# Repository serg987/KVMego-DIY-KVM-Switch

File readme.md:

# KVM Switch and related projects

## Quick links:

[KVM Switch - ATMega Microship studio project](kvm_switch/)

[KVM Switch - Kicad project](kvm_switch/pcb_kicad/)

[Video switches in general](video_switches/)

[I2C Switch - A hack for EDID sharing, ATTiny85 project](video_switches/i2c_switch/)

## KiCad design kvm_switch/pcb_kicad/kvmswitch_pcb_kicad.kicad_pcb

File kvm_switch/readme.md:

# KVMego KVM Switch

## Why?

The market for KVM switches is quite wide, but it is difficult to find one that properly fits someone's needs. The main disadvantage is that they are manufactured as single units, where video and keyboard/mouse switches are housed in the same enclosure. This not only forces users to deal with numerous thick cables but also limits their options. Some switches may have EDID support but lack hotkey support, while others may not have enough display ports or support for needed resolutions. However, the main problem is that most switches implement just an ordinary USB switch that disconnects displays, keyboards, and mice from inactive computers, making it possible to detect when the switch is being used. Additionally, KVM switches usually do not support a mouse jiggler function, which allows inactive computers to stay awake while not in use.

This project attempts to resolve most of these issues.

## Description

### Main Features:
- **Modular architecture**: The keyboard/mouse control unit is separated from video switches, allowing users to either use existing switches or create custom video switches. A video switch may be directly plugged into a monitor, requiring fewer thick video cables.
- **Persistent USB connection**: Once the KVM switch is connected to a computer's USB port, it is never disconnected, making it impossible to detect switching by disconnection.
- **Integrated controls**: All controls and indicators are built into the keyboard; no separate buttons or LEDs are needed. The unit can be hidden from view.
- **Built-in mouse jiggler**: Keeps computers awake, both active and inactive ones.
- **Cost-effective components**: Uses development modules that require no high-precision soldering.
- **Plain C ATMega code**: No USB stack required, easily adaptable to individual needs.

### Known Limitations:
- **USB wire connections**: The unit connects to computers via USB wires. Not many keyboard and mouse types have been tested, but it has worked with all tested devices, including wireless mice with 2.4GHz USB dongle.
- **USB-only switching**: Only USB keyboards and mice can be switched between computers. However, with an external USB switch and some adaptation, other devices may be connected.
- **No VID/PID copying**: A computer will see a standard HID device with the CH9350L signature rather than the original device signature.
- **Processing delays**: USB-UART-CPU-UART-USB processing introduces delays up to several dozen milliseconds, though this is not noticeable during normal use.
- **Video switch requirement**: Still requires video switches. Existing switches must be adapted to use plain on/off signals or require code adaptation. RF-controlled custom video switches are supported via RF transmitter code.
- **Three-computer limit**: Currently supports up to 3 computers.
- **HID packet structure dependency**: Different HID devices have varying UART packet structures, which is critical for the jiggler function. Currently, 4 types of mouse packets are recognized, so the jiggler may not work with some mice, though main switch functionality should remain unaffected.
- **No hot-plugging**: Due to different mouse types, mice cannot be hot-plugged as the jiggler may stop working. The switch must be fully disconnected from all computers to change the mouse.

## Compiling and programming

The project uses Microchip Studio as the IDE, so all settings are configured there. By default, it targets the ATMega2560 with the 'DEBUG' configuration, which produces slightly larger code. If debugging is not needed, switch to the 'Release' target for optimized builds.

Fuses for ATMega:

### Build Configuration Options:

#### LCD_DEBUG
When `LCD_DEBUG` is defined in `src/common/config.h`, the system enables debug information output to a 1602 LCD display. This feature:
- Displays error messages and system status information
- Shows various error codes including:
  - `E: UnknCmdM XX` - Unknown command byte from master (XX = hex value)
  - `E: UnknCmdS X XX` - Unknown command byte from slave (X = channel, XX = hex value)
  - `E: KbMsDaSzEx XX` - Keyboard/Mouse data size exceeded (XX = size)
  - `E: VPSizeEx XX` - VID/PID data size exceeded (XX = size)
  - `E: QueueOvrflw` - Scheduler queue overflow
- When LCD is not going to be used, comment out `#define LCD_DEBUG` in config.h

#### RF_TRANSMITTER
When `RF_TRANSMITTER` is defined in `src/common/config.h`, the video control lines become active (low level) for 2 seconds only during
the switching. This allow to contol the 433MHz RF encoded transmitter with 4 buttons:
- See `videoSwitchControl.c` for implementation details
- For simple continuous high-level video control signals, comment out `#define RF_TRANSMITTER` in config.h

## User Manual

### Initial Setup
Always connect the device to a PC with the operating system turned on, logged in, and not in sleep mode. There have been reported issues with macOS (likely hardware-related and possibly connected to power management) where the CH9350L fails to initialize. See the Known Issues section for details.

### LCD Display Messages
If an LCD is connected and `LCD_DEBUG` is enabled, you will see various status and error messages:

**System Status Messages:**
- Normal operation displays current PC connection status
- Error messages appear when issues occur (see LCD_DEBUG section above)
- Messages alternate between lines to show multiple pieces of information

**Error Indicators:**
- Errors are displayed with prefixes like "E: " followed by specific error codes
- Unknown command errors show the problematic byte value in hexadecimal
- Size exceeded errors indicate buffer overflows
- Queue overflow indicates the scheduler is overloaded

### Single PC Usage
The device can be used with a single PC if only the jiggler functionality is needed without additional device connections.

### Control Interface
Everything is controlled by double-pressing the 'ScrollLock' button, which starts the control sequence.

#### Control Sequence:
1. **Initiate control mode**: Double-press 'ScrollLock'
2. **Visual feedback**: All three keyboard LEDs will blink once
3. **Current state display**: LEDs will blink to show the current switching mode state (e.g., if current PC is 2, the CapsLock LED will blink)
4. **Command input**: You can proceed with a command without waiting for the blinking to stop
5. **New state confirmation**: After state change, LEDs will blink to show the new state
6. **Error indication**: If there's an error (requested PC not connected or unsupported control button), all 3 LEDs will blink rapidly
7. **Auto-exit**: The device automatically exits control mode after 6 seconds of inactivity
8. **LED restoration**: After exiting control mode, LEDs return to displaying the keyboard state of the connected PC

#### PC Switching Commands:
- `2 × ScrollLock + [1-3]` - Switch to PC connected to the corresponding port
- `2 × ScrollLock + 0` (or `+` or `Enter`) - Rolling switch to the next PC with increasing number
- `2 × ScrollLock + -` - Rolling switch to the next PC with decreasing number

*Note: Numeric keys, +/- keys, and Enter work from both the main keyboard layout and the numpad.*

#### Jiggler Control:
The jiggler simulates mouse movements as arcs with random speed, length, and time between movements to prevent computers from entering sleep mode.

**Jiggler Control Mode:**
- Access: `2 × ScrollLock + J`
- **Confirmation**: All LEDs blink once after pressing 'J'
- **Toggle functionality**: Unlike PC switching, jiggler can be toggled on and off for each PC
- **State display**: Shows current jiggler state by blinking LEDs for PCs where jiggler is active
- **No active indication**: If no PC has active jiggler, no LEDs will blink before or after commands

**Jiggler Commands:**
- `2 × ScrollLock + J + [1-3]` - Toggle jiggler for the corresponding PC
- `2 × ScrollLock + J + 0` - Toggle jiggler for the current PC

**Jiggler Timing:**
- **Active PC**: When jiggler is enabled for the currently connected PC, it waits 2 minutes after the last mouse movement or keypress before starting
- **Inactive PC**: When jiggler is enabled for an inactive PC, it starts with the next scheduled jiggler cycle (maximum 25 seconds)

## Video Switches

Video switches should be connected to the video control output. In most cases, this requires a custom solution. The author used inexpensive HDMI switches with added RF receivers to reduce cable clutter. This option will be described in the repository documentation (to be added later), but any solution suitable for a user's setup can be implemented.

The system provides three on/off outputs for controlling video switches, connected via a USB-C connector for the video control cable. **Note**: This is NOT a USB connection; USB-C cables are used purely for convenience due to their thin profile when connecting to video and/or USB switches.

## Schematics

### Design
To avoid working with embedded USB stacks, CH9350L ICs are used for USB communication. These ICs function as host/master HID-class USB devices and convert USB packets to UART packets. The system uses 4 CH9350L chips: one master device for keyboard and mouse connection, and 3 for computer connections. If only 2 computers are needed, only 3 CH9350L chips are required.

### Core Components
**CPU**: ATMega640/1280/2560 processes all UART packets, controls data flow, and prepares jiggler sequences.

**Why ATMega?** 
- Has exactly the computing power needed for this application
- Lacks peripherals that could potentially leak user data (critical for keyboard security)
- One of a few available microcontrollers on the market with 4 hardware UARTs at a reasonable price and a lot of development boards
- Available development boards make prototyping easier
- Author's familiarity with the platform

### Power Management
The +5V power from computers is isolated using Schottky diodes and processed through a DC-DC step-up converter to maintain +5.0V. This is optional - the prototype board worked without the converter using only Schottky diodes, operating at Vcc~4.7V.

### Debug and Development Features
The schematic and board include:
- **10-pin connector**: For 8-channel logic analyzer
- **ISP** and **JTAG** connectors: For programming and debugging
- **1602 LCD**: Displays debug information (not required for normal operation)
- **Connection monitoring resistors** (R18-R20 and R22-R24): For monitoring computer connections (not currently used in code, reserved for future edge case handling)

### Implementation Options

#### Development Board Implementation
The unit can be implemented using prototype boards with development modules. Various modules for ATMega2560 and CH9350L are available on Aliexpress and other marketplaces.

**Important considerations:**
- Most ATMega2560 modules use 16 MHz crystal resonators, which must be replaced with 14.7456 MHz ones
- Development boards typically have USB-UART chips connected to UART0 pins - either remove their resistors or cut the PCB tracks

The first hardware prototype used development boards

The original Aliexpress links used by author are no longer available, probably due to US tariffs, but something similar has been found:
 - Mega 2560 PRO MINI Board - https://www.aliexpress.us/item/3256807606413251.html
 - CH9350L module with 2xUSB-A sockets https://www.aliexpress.us/item/3256806492553287.html
 - USB-A M to USB-B F adapter https://www.aliexpress.us/item/3256805907770571.html

#### Custom PCB Implementation
The custom PCB includes both USB-B and USB-C footprints for computer connections - solder whichever connector type is suitable for your setup.

The PCB is available to order on [PCBWay](https://www.pcbway.com/project/shareproject/KVMego_A_modular_undetectable_KVM_switch_with_a_built_in_mouse_jiggler_c0eef20d.html)

### Resource Utilization

#### ATMega2560 Resources Used:
- **UART0**: 'Master' CH9350, connected to keyboard and mouse
- **UART1-3**: 'Slave' CH9350s, connected to PCs
- **TIMER4**: Exclusively for scheduler (T = ~500 μs)
- **TIMER3**: F=Fosc, for seeding random generator (may be reused after initialization, but currently not needed)

#### Component Requirements
**Essential components:**
- ATMega with crystal and supporting discrete components
- CH9350L chips with their discrete components and USB connectors
- Schottky diodes

**For prototype implementation:** Only ATMega development board and 2-4 CH9350L boards are needed. This approach avoids tedious soldering and is often cheaper than buying components separately.

## Known Issues

### Hardware Issues
**PCB Gerbers**: The PCB gerbers currently on PCBWay have a cosmetic issue - the ISP connector is incorrectly labeled as JTAG. The schematic and PCB in the repository include the JTAG connector, but this version has not gone to production.

### Software Limitations
**Mouse Hot-plugging**: Due to different mouse types sending different frame structures, mice cannot be hot-plugged as the jiggler may stop working. Reinitializing the jiggler on-the-fly is challenging and not currently implemented.

### Platform-Specific Issues
**macOS Compatibility**: 
- **Symptoms**: Exact reproduction steps are unknown, but the issue occurred when the switch was connected to a Mac via a dock station and disconnected while the Mac was in sleep mode
- **Behavior**: Upon reconnection, CH9350L fails to initialize and continuously responds with '57 AB 12 00 00 00 00 00 FF AC 20' to '57 AB 82 A3' requests
- **Resolution**: Disconnect and reconnect the dock station while the OS is awake (reconnecting the switch alone while OS is awake does not resolve the issue)

## Development

### Testing Framework
Critical code has unit test coverage located in the [atmswitch_uts](atmswitch_uts/) directory. This is a Ceedling project with setup [instructions](atmswitch_uts/test/readme.md).

### Contributing
When modifying the code:
1. Note that the main loop should be no longer than 2 bytes at 115.2Kbaud - ~170us. Even there are buffers on the receiver sides, 
the overflow would make things worse, so to be on the safe side do not allow the main loop grow. Split heavy computing tasks
on multiple steps and schedule them
2. Ensure unit tests pass for any changed modules
3. Test with multiple keyboard and mouse types if modifying input handling
4. Verify jiggler functionality
5. Test all hotkey combinations

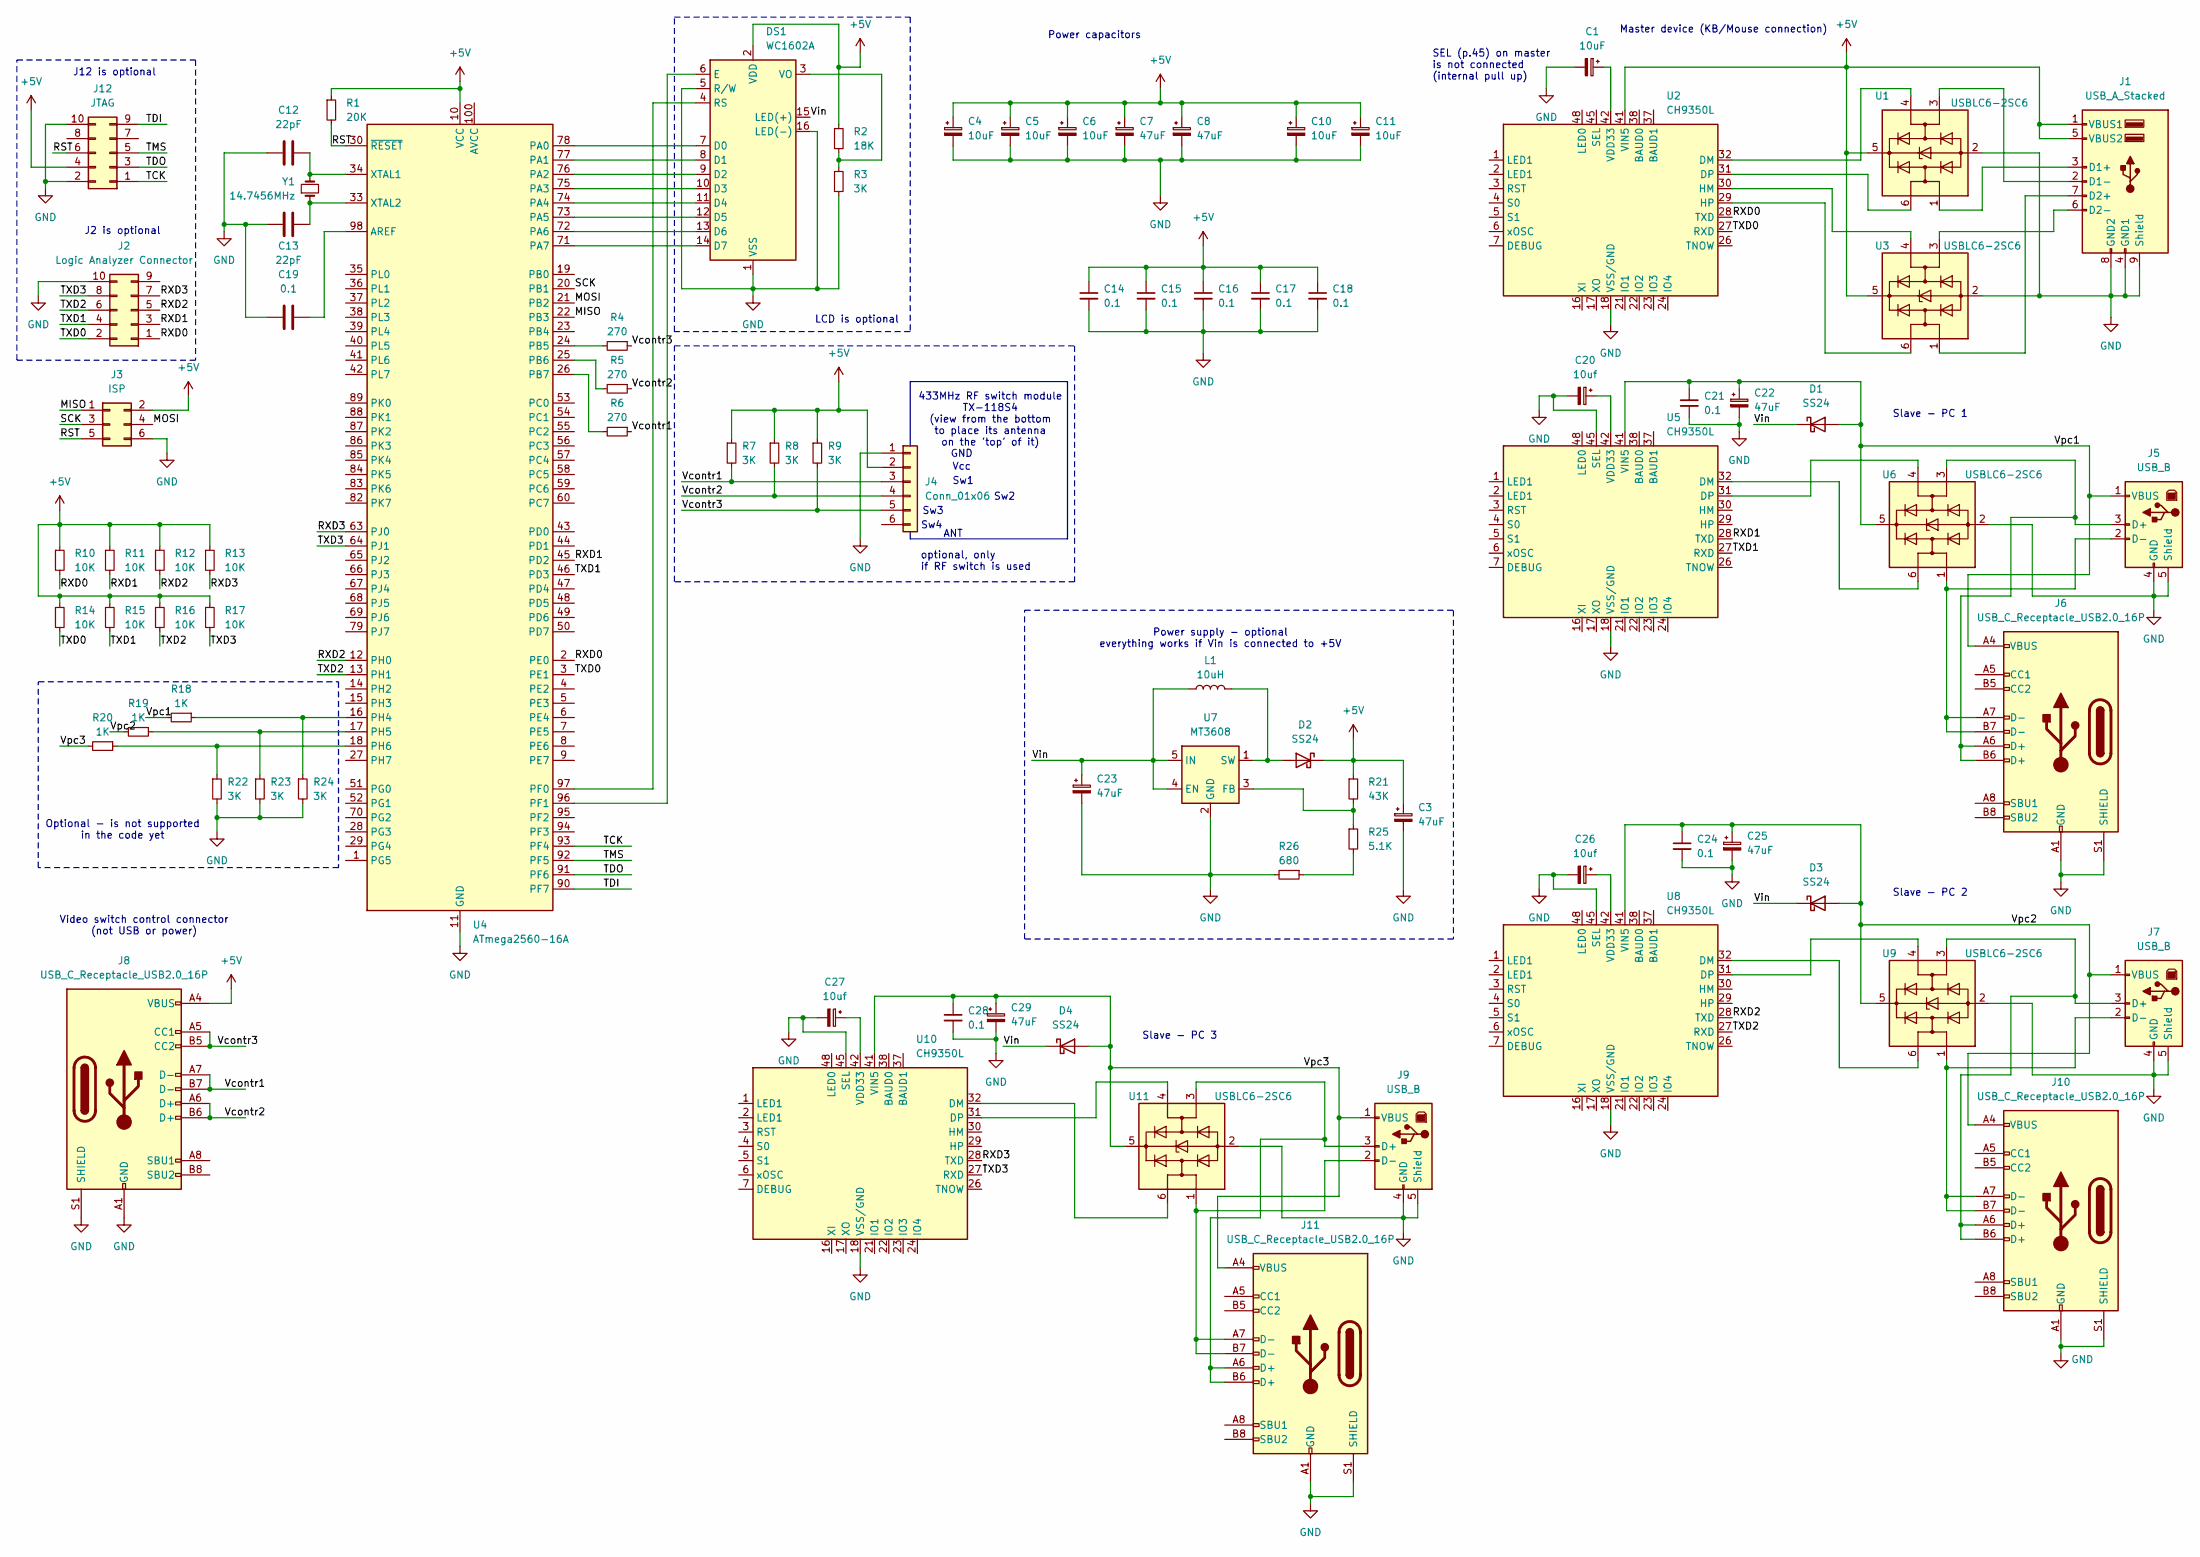
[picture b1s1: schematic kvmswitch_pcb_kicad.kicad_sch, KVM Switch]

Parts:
C1, C4, C5, C6, C10, C11: 10uF; CP_EIA-3216-12_Kemet-S_Pad1.58x1.35mm_HandSolder
C3, C7, C8, C22, C23, C25, C29: 47uF; CP_EIA-3216-12_Kemet-S_Pad1.58x1.35mm_HandSolder
C12, C13: 22pF; C_1206_3216Metric_Pad1.33x1.80mm_HandSolder
C14, C15, C16, C17, C18, C19, C21, C24, C28: 0.1; C_1206_3216Metric_Pad1.33x1.80mm_HandSolder
C20, C26, C27: 10uf; CP_EIA-3216-12_Kemet-S_Pad1.58x1.35mm_HandSolder
D1, D2, D3, D4: SS24; D_SMA_Handsoldering
DS1: WC1602A
J1: USB_A_Stacked; USB_A_Wuerth_61400826021_Horizontal_Stacked
J2: Logic Analyzer Connector; PinHeader_2x05_P2.54mm_Vertical
J3: ISP; PinHeader_2x03_P2.54mm_Vertical
J4: Conn_01x06; PinHeader_1x06_P2.54mm_Vertical
J5, J7, J9: USB_B; USB_B_OST_USB-B1HSxx_Horizontal
J6, J8, J10, J11: USB_C_Receptacle_USB2.0_16P; USB_C_Receptacle_HCTL_HC-TYPE-C-16P-01A_CUSTOM
J12: JTAG; PinHeader_2x05_P2.54mm_Vertical
L1: 10uH; L_Wuerth_HCI-1040
R1: 20K; R_1206_3216Metric_Pad1.30x1.75mm_HandSolder
R2: 18K; R_1206_3216Metric_Pad1.30x1.75mm_HandSolder
R3, R7, R8, R9, R22, R23, R24: 3K; R_1206_3216Metric_Pad1.30x1.75mm_HandSolder
R4, R5, R6: 270; R_1206_3216Metric_Pad1.30x1.75mm_HandSolder
R10, R11, R12, R13, R14, R15, R16, R17: 10K; R_1206_3216Metric_Pad1.30x1.75mm_HandSolder
R18, R19, R20: 1K; R_1206_3216Metric_Pad1.30x1.75mm_HandSolder
R21: 43K; R_1206_3216Metric_Pad1.30x1.75mm_HandSolder
R25: 5.1K; R_1206_3216Metric_Pad1.30x1.75mm_HandSolder
R26: 680; R_1206_3216Metric_Pad1.30x1.75mm_HandSolder
U1, U3, U6, U9, U11: USBLC6-2SC6; SOT-23-6
U2, U5, U8, U10: CH9350L; LQFP-48_7x7mm_P0.5mm
U4: ATmega2560-16A; TQFP-100_14x14mm_P0.5mm
U7: MT3608; SOT-23-6_Handsoldering
Y1: 14.7456MHz; Crystal_HC49-4H_Vertical

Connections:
+5V: C3.1, C4.1, C5.1, C6.1, C7.1, C8.1, C10.1, C11.1, C14.1, C15.1, C16.1, C17.1, C18.1, D2.1 (K), DS1.2 (VDD), J1.1 (VBUS1), J1.5 (VBUS2), J3.2, J4.2, J8.A4 (VBUS), J8.A9 (VBUS), J8.B4 (VBUS), J8.B9 (VBUS), J12.4, R1.1, R2.1, R7.1, R8.1, R9.1, R10.1, R11.1, R12.1, R13.1, R14.1, R15.1, R16.1, R17.1, R21.1, U1.5 (VBUS), U2.41 (VIN5), U3.5 (VBUS), U4.10 (VCC), U4.31 (VCC), U4.61 (VCC), U4.80 (VCC)
/MISO: J3.1, U4.22 (PB3)
/MOSI: J3.4, U4.21 (PB2)
/RST: J3.5, J12.6, R1.2, U4.30 (~RESET)
/RXD0: J2.1, R10.2, U2.28 (TXD), U4.2 (PE0)
/RXD1: J2.3, R11.2, U4.45 (PD2), U5.28 (TXD)
/RXD2: J2.5, R12.2, U4.12 (PH0), U8.28 (TXD)
/RXD3: J2.7, R13.2, U4.63 (PJ0), U10.28 (TXD)
/SCK: J3.3, U4.20 (PB1)
/TCK: J12.1, U4.93 (PF4)
/TDI: J12.9, U4.90 (PF7)
/TDO: J12.3, U4.91 (PF6)
/TMS: J12.5, U4.92 (PF5)
/TXD0: J2.2, R14.2, U2.27 (RXD), U4.3 (PE1)
/TXD1: J2.4, R15.2, U4.46 (PD3), U5.27 (RXD)
/TXD2: J2.6, R16.2, U4.13 (PH1), U8.27 (RXD)
/TXD3: J2.8, R17.2, U4.64 (PJ1), U10.27 (RXD)
/Vcontr1: J4.3, J8.A7 (D-), J8.B7 (D-), R6.1, R7.2
/Vcontr2: J4.4, J8.A6 (D+), J8.B6 (D+), R5.1, R8.2
/Vcontr3: J4.5, J8.A5 (CC1), J8.B5 (CC2), R4.1, R9.2
/Vin: C23.1, D1.1 (K), D3.1 (K), D4.1 (K), DS1.15 (LED(+)), L1.1, U7.4 (EN), U7.5 (IN)
/Vpc1: C21.1, C22.1, D1.2 (A), J5.1 (VBUS), J6.A4 (VBUS), J6.A9 (VBUS), J6.B4 (VBUS), J6.B9 (VBUS), R18.2, U5.41 (VIN5), U6.5 (VBUS)
/Vpc2: C24.1, C25.1, D3.2 (A), J7.1 (VBUS), J10.A4 (VBUS), J10.A9 (VBUS), J10.B4 (VBUS), J10.B9 (VBUS), R19.2, U8.41 (VIN5), U9.5 (VBUS)
/Vpc3: C28.1, C29.1, D4.2 (A), J9.1 (VBUS), J11.A4 (VBUS), J11.A9 (VBUS), J11.B4 (VBUS), J11.B9 (VBUS), R20.2, U10.41 (VIN5), U11.5 (VBUS)
GND: C1.2, C3.2, C4.2, C5.2, C6.2, C7.2, C8.2, C10.2, C11.2, C12.1, C13.1, C14.2, C15.2, C16.2, C17.2, C18.2, C19.1, C20.2, C21.2, C22.2, C23.2, C24.2, C25.2, C26.2, C27.2, C28.2, C29.2, DS1.1 (VSS), DS1.5 (R/W), DS1.16 (LED(-)), J1.4 (GND1), J1.8 (GND2), J1.9 (Shield), J2.10, J3.6, J4.1, J5.4 (GND), J5.5 (Shield), J6.A1 (GND), J6.A12 (GND), J6.B1 (GND), J6.B12 (GND), J6.S1 (SHIELD), J7.4 (GND), J7.5 (Shield), J8.A1 (GND), J8.A12 (GND), J8.B1 (GND), J8.B12 (GND), J8.S1 (SHIELD), J9.4 (GND), J9.5 (Shield), J10.A1 (GND), J10.A12 (GND), J10.B1 (GND), J10.B12 (GND), J10.S1 (SHIELD), J11.A1 (GND), J11.A12 (GND), J11.B1 (GND), J11.B12 (GND), J11.S1 (SHIELD), J12.2, J12.10, R3.2, R22.2, R23.2, R24.2, R26.2, U1.2 (GND), U2.18 (VSS/GND), U3.2 (GND), U4.11 (GND), U4.32 (GND), U4.62 (GND), U4.81 (GND), U4.99 (GND), U5.18 (VSS/GND), U5.45 (SEL), U6.2 (GND), U7.2 (GND), U8.18 (VSS/GND), U8.45 (SEL), U9.2 (GND), U10.18 (VSS/GND), U10.45 (SEL), U11.2 (GND)
unnamed: D2.2 (A), L1.2, U7.1 (SW)
unnamed: DS1.7 (D0), U4.78 (PA0)
unnamed: DS1.8 (D1), U4.77 (PA1)
unnamed: DS1.9 (D2), U4.76 (PA2)
unnamed: DS1.10 (D3), U4.75 (PA3)
unnamed: DS1.11 (D4), U4.74 (PA4)
unnamed: DS1.12 (D5), U4.73 (PA5)
unnamed: DS1.13 (D6), U4.72 (PA6)
unnamed: DS1.14 (D7), U4.71 (PA7)
unnamed: DS1.6 (E), U4.96 (PF1)
unnamed: DS1.4 (RS), U4.97 (PF0)
unnamed: DS1.3 (VO), R2.2, R3.1
unnamed: J1.3 (D1+), U1.1 (I/O1)
unnamed: J1.2 (D1-), U1.3 (I/O2)
unnamed: J1.7 (D2+), U3.1 (I/O1)
unnamed: J1.6 (D2-), U3.3 (I/O2)
unnamed: J5.3 (D+), J6.A6 (D+), J6.B6 (D+), U6.3 (I/O2)
unnamed: J5.2 (D-), J6.A7 (D-), J6.B7 (D-), U6.1 (I/O1)
unnamed: J7.3 (D+), J10.A6 (D+), J10.B6 (D+), U9.3 (I/O2)
unnamed: J7.2 (D-), J10.A7 (D-), J10.B7 (D-), U9.1 (I/O1)
unnamed: J9.3 (D+), J11.A6 (D+), J11.B6 (D+), U11.3 (I/O2)
unnamed: J9.2 (D-), J11.A7 (D-), J11.B7 (D-), U11.1 (I/O1)
unnamed: R25.2, R26.1
unnamed: U1.4 (I/O2), U2.32 (DM)
unnamed: U1.6 (I/O1), U2.31 (DP)
unnamed: U2.30 (HM), U3.4 (I/O2)
unnamed: U2.29 (HP), U3.6 (I/O1)
unnamed: C1.1, U2.42 (VDD33)
unnamed: C19.2, U4.98 (AREF)
unnamed: R4.2, U4.24 (PB5)
unnamed: R5.2, U4.25 (PB6)
unnamed: R6.2, U4.26 (PB7)
unnamed: R18.1, R24.1, U4.16 (PH4)
unnamed: R19.1, R23.1, U4.17 (PH5)
unnamed: R20.1, R22.1, U4.18 (PH6)
unnamed: C12.2, U4.34 (XTAL1), Y1.2
unnamed: C13.2, U4.33 (XTAL2), Y1.1
unnamed: U5.32 (DM), U6.6 (I/O1)
unnamed: U5.31 (DP), U6.4 (I/O2)
unnamed: C20.1, U5.42 (VDD33)
unnamed: R21.2, R25.1, U7.3 (FB)
unnamed: U8.32 (DM), U9.6 (I/O1)
unnamed: U8.31 (DP), U9.4 (I/O2)
unnamed: C26.1, U8.42 (VDD33)
unnamed: U10.32 (DM), U11.6 (I/O1)
unnamed: U10.31 (DP), U11.4 (I/O2)
unnamed: C27.1, U10.42 (VDD33)

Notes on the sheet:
Power supply - optional everything works if Vin is connected to +5V
Optional - is not supported in the code yet
Slave - PC 2
Master device (KB/Mouse connection)
Vcc
Sw4
433MHz RF switch module TX-118S4 (view from the bottom to place its antenna on the 'top' of it)
ANT
LCD is optional
Slave - PC 1
Sw1
Sw3
Sw2
Power capacitors
J2 is optional
SEL (p.45) on master is not connected (internal pull up)
GND
J12 is optional
Video switch control connector (not USB or power)
Slave - PC 3
optional, only if RF switch is used

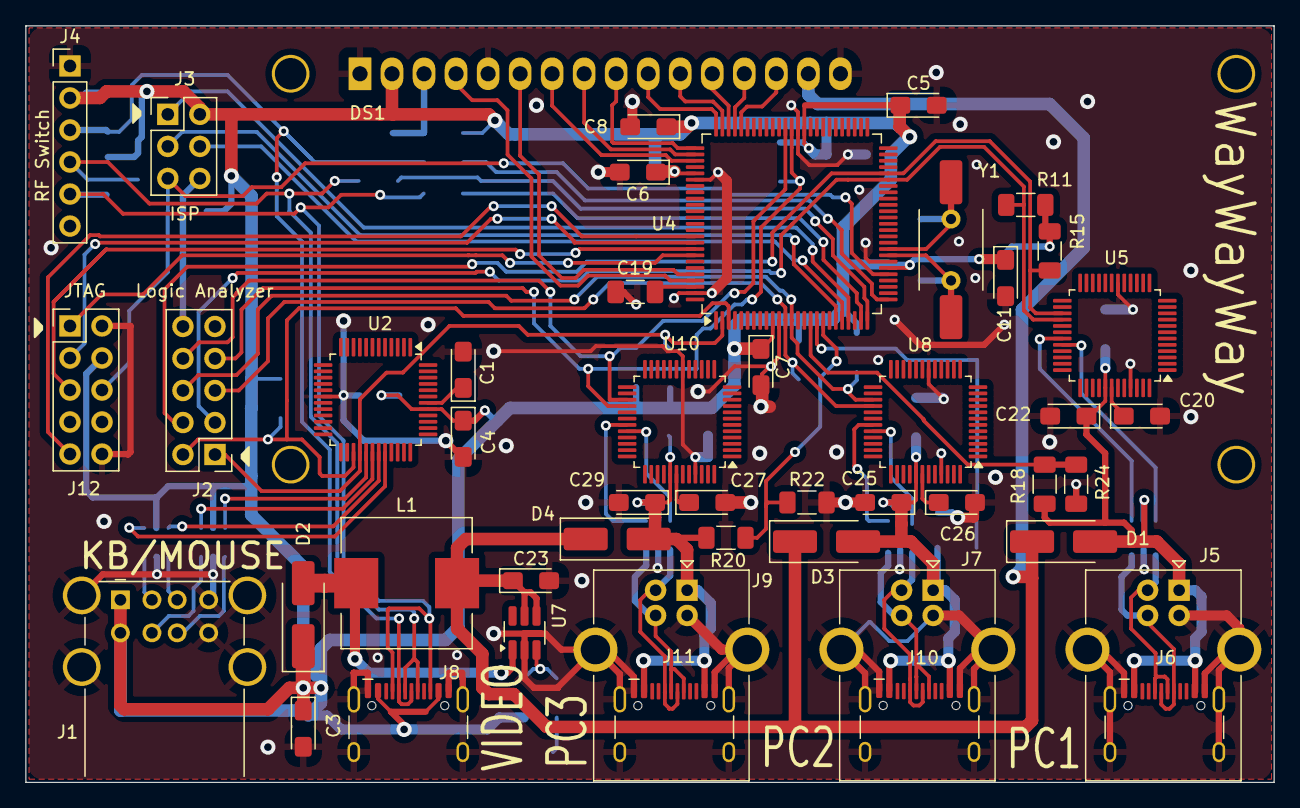
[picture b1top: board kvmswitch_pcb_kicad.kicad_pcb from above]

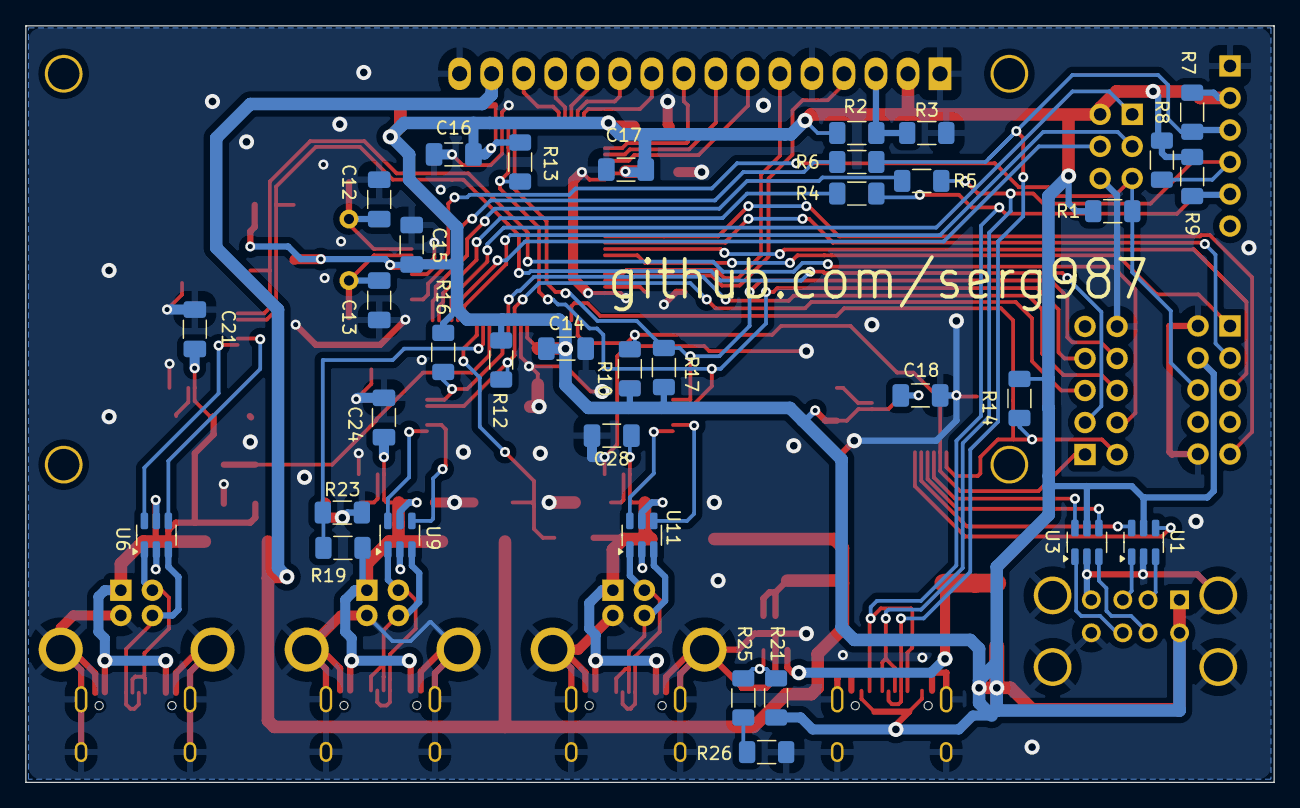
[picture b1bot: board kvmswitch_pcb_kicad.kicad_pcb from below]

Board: 2 copper layers, 99.0 x 60.0 mm, 82 parts (35 on the bottom side), 72 nets.

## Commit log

2025-07-04 Add pcbway link
